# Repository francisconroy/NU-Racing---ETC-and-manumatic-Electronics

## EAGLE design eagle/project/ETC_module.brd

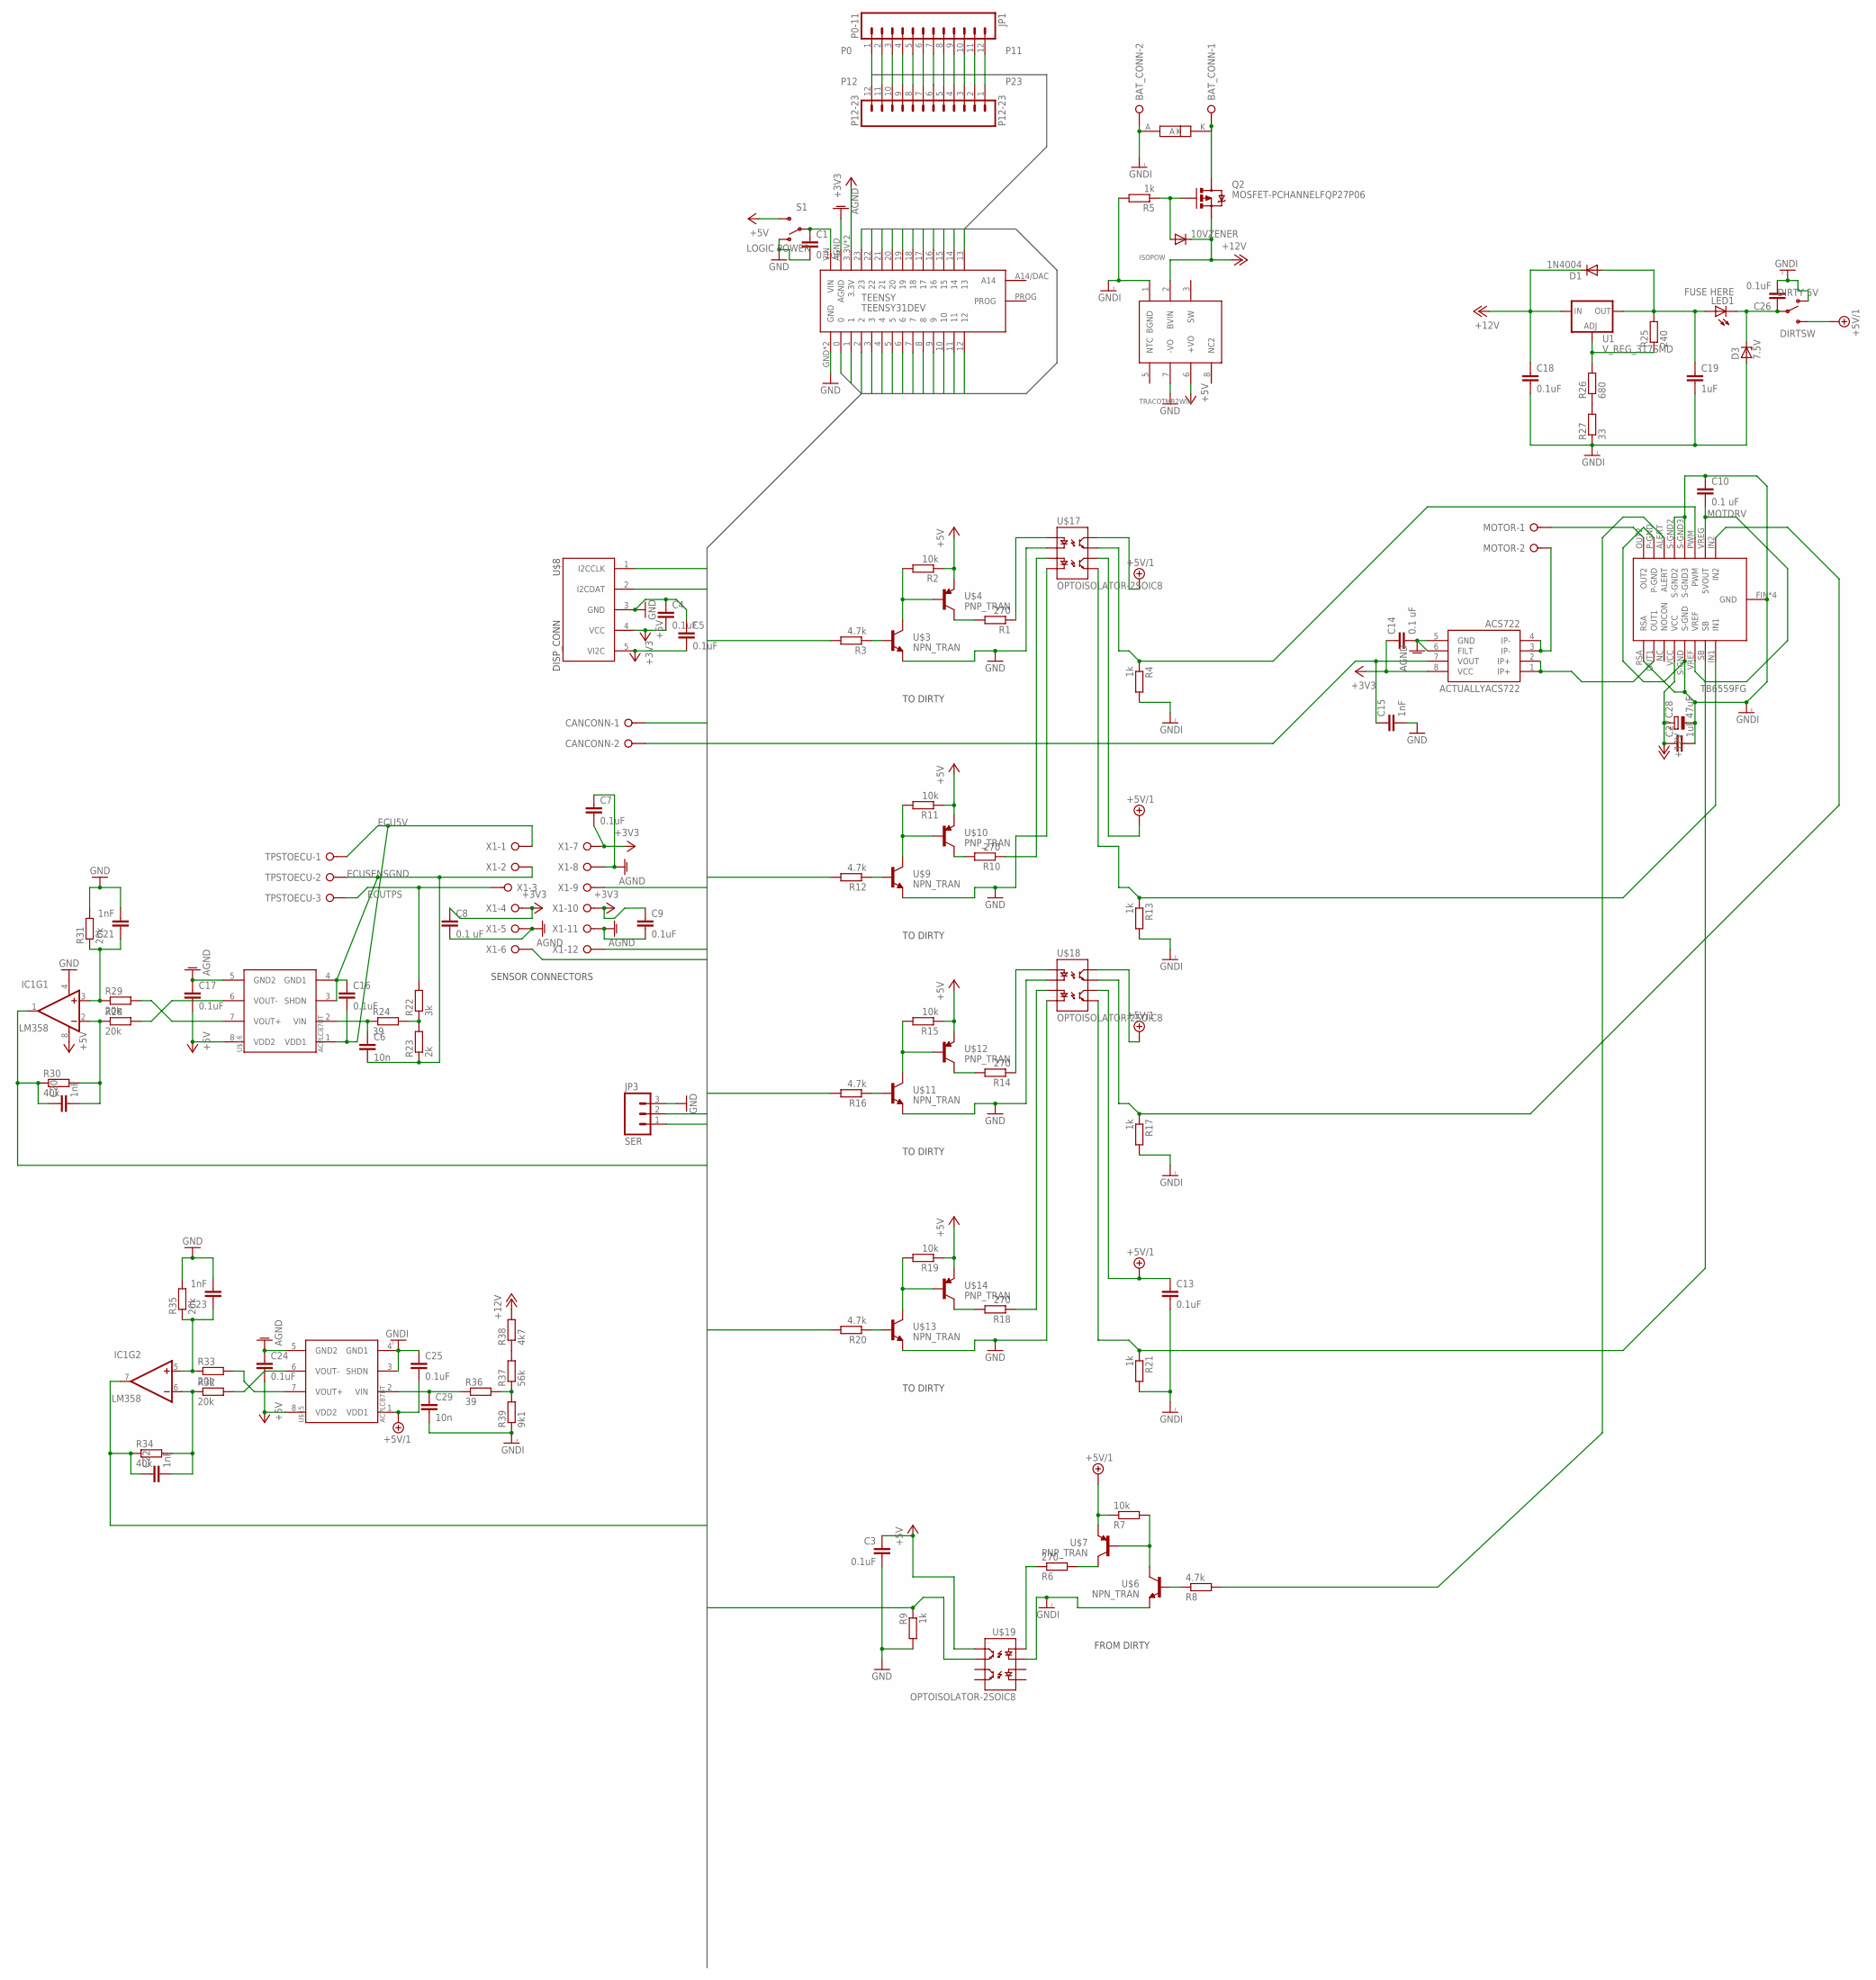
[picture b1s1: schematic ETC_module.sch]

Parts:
10VZENER: DIODE-DO214BA; DO214BA
ACTUALLYACS722: ACS722; SO08
BAT_CONN: W237-02P; W237-132
C1, C3, C4, C5, C7, C9, C13, C16, C17, C18, C24, C25, C26: 0.1uF; C1206
C6, C29: 10n; C1206
C8, C10, C14: 0.1 uF; C1206
C15, C20, C21, C22, C23: 1nF; C1206
C19, C27: 1uF; C1206
C28: 47uF; E5-8,5
CANCONN: W237-02P; W237-132
D1: 1N4004; DO41-10
D3: 7.5V; ZDIO-7.5
DIRTSW: DIRTY 5V; SWITCH-SPDT_KIT
IC1: LM358; DIP08
ISOPOW: TRACOTMR2WIN; TRACOPOWERDC-DCTRM2WIN
JP1: P0-11; 1X12_LOCK
JP3: SER; MOLEX-1X3_LOCK
LED1: FUSE HERE; LED-1206
MOTDRV: TB6559FG; HSOP16-P-300-1.00
MOTOR: W237-02P; W237-132
P12-23: P12-23; 1X12_LOCK
Q2: MOSFET-PCHANNELFQP27P06; TO220V
R1, R6, R10, R14, R18: 270; R1206
R2, R7, R11, R15, R19: 10k; R1206
R3, R8, R12, R16, R20: 4.7k; R1206
R4, R5, R9, R13, R17, R21: 1k; R1206
R22: 3k; M1206
R23: 2k; M1206
R24, R36: 39; R1206
R25: 240; R1206
R26: 680; R1206
R27: 33; R1206
R28, R29, R31, R32, R33, R35: 20k; R1206
R30, R34: 40k; R1206
R37: 56k; R1206
R38: 4k7; R1206
R39: 9k1; R1206
S1: LOGIC POWER; SWITCH-SPDT_KIT
TEENSY: TEENSY31DEV; TEENSY31PAC
TPSTOECU: W237-03P; W237-133
U1: V_REG_317SMD; SOT223
U$1: LNBTVS; JEDECDO-214AB
U$3, U$6, U$9, U$11, U$13: NPN_TRAN; SOT23-3
U$4, U$7, U$10, U$12, U$14: PNP_TRAN; SOT23-3
U$8: DISP_CONN
U$15, U$16: ACPLC87BT; SO8STRETCH
U$17, U$18, U$19: OPTOISOLATOR-2SOIC8; SO08-2
X1: W237-12P

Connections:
5VOUT: C10.2, MOTDRV.VREF, MOTDRV.VREG (5VOUT)
+3V3: ACTUALLYACS722.8 (VCC), C5.2, C7.2, C8.1, C9.1, C14.1, TEENSY.3.3V, TEENSY.3.3VV (3.3V), U$8.5 (VI2C), X1.4, X1.7, X1.10
+5V/1: C13.1, C25.2, DIRTSW.3 (S), R7.1, U$7.2 (E), U$15.1 (VDD1), U$17.6 (CL2), U$17.8 (CL1), U$18.6 (CL2), U$18.8 (CL1)
+5VCLEAN: C3.1, C4.2, C17.2, C24.2, IC1.8 (V+), ISOPOW.6 (+VO), R2.1, R11.1, R15.1, R19.1, S1.3 (S), U$4.2 (E), U$8.4 (VCC), U$10.2 (E), U$12.2 (E), U$14.2 (E), U$15.8 (VDD2), U$16.8 (VDD2), U$19.8 (CL1)
AGND: ACTUALLYACS722.5 (GND), ACTUALLYACS722.6 (FILT), C7.1, C8.2, C9.2, C14.2, C17.1, C24.1, TEENSY.AGND, U$15.5 (GND2), U$16.5 (GND2), X1.5, X1.8, X1.11
ECU5V: C16.2, TPSTOECU.1, U$16.1 (VDD1), X1.1
ECUSENSGND: C6.2, C16.1, R23.1, TPSTOECU.2, U$16.3 (SHDN), U$16.4 (GND1), X1.2
ECUTPS: R22.2, TPSTOECU.3, X1.3
GND: C1.2, C3.2, C4.1, C5.1, C15.2, C21.2, C23.2, IC1.4 (V-), ISOPOW.7 (-VO), JP3.3, R9.2, R31.2, R35.2, S1.1 (O), TEENSY.GND, TEENSY.GND2 (GND), U$3.2 (E), U$8.3 (GND), U$9.2 (E), U$11.2 (E), U$13.2 (E), U$17.2 (C1), U$17.4 (C2), U$18.2 (C1), U$18.4 (C2)
GNDI: BAT_CONN.2, C10.1, C13.2, C18.2, C19.2, C25.1, C26.2, C27.2, C28.-, C29.2, D3.A, DIRTSW.1 (O), ISOPOW.1 (BGND), MOTDRV.FIN (GND), MOTDRV.FIN2 (GND), MOTDRV.P$4 (GND), MOTDRV.P$20 (GND), MOTDRV.P-GND, MOTDRV.RSA, MOTDRV.S-GND, MOTDRV.S-GND2, MOTDRV.S-GND3, R4.2, R5.2, R13.2, R17.2, R21.2, R27.1, R39.1, U$1.A, U$6.2 (E), U$15.3 (SHDN), U$15.4 (GND1), U$19.2 (C1)
unnamed: R2.2, U$3.3 (C), U$4.1 (B)
unnamed: C1.1, S1.2, TEENSY.VIN
unnamed: R1.1, U$17.1 (A1)
unnamed: R1.2, U$4.3 (C)
unnamed: R3.1, U$3.1 (B)
unnamed: R7.2, U$6.3 (C), U$7.1 (B)
unnamed: 10VZENER.A, Q2.1 (G), R5.1
unnamed: MOTDRV.PWM, R4.1, U$17.7 (EM1)
unnamed: R6.1, U$19.1 (A1)
unnamed: R6.2, U$7.3 (C)
unnamed: R8.1, U$6.1 (B)
unnamed: R19.2, U$13.3 (C), U$14.1 (B)
unnamed: R18.1, U$18.3 (A2)
unnamed: C26.1, D3.C, DIRTSW.2, LED1.C
unnamed: R37.2, R38.1
unnamed: C19.1, D1.A, LED1.A, R25.2, U1.2 (OUT)
unnamed: R11.2, U$9.3 (C), U$10.1 (B)
unnamed: MOTDRV.OUT2, MOTOR.1
unnamed: ACTUALLYACS722.1 (IP+), ACTUALLYACS722.2 (IP+), MOTDRV.OUT1
unnamed: R10.1, U$17.3 (A2)
unnamed: R10.2, U$10.3 (C)
unnamed: R12.1, U$9.1 (B)
unnamed: R15.2, U$11.3 (C), U$12.1 (B)
unnamed: R14.1, U$18.1 (A1)
unnamed: R14.2, U$12.3 (C)
unnamed: R16.1, U$11.1 (B)
unnamed: MOTDRV.IN2, R17.1, U$18.7 (EM1)
unnamed: R18.2, U$14.3 (C)
unnamed: R20.1, U$13.1 (B)
unnamed: MOTDRV.ALERT, R8.2
unnamed: MOTDRV.SB, R21.1, U$18.5 (EM2)
unnamed: ACTUALLYACS722.3 (IP-), ACTUALLYACS722.4 (IP-), MOTOR.2
unnamed: C6.1, R24.1, U$16.2 (VIN)
unnamed: R22.1, R23.2, R24.2
unnamed: R26.1, R27.2
unnamed: R25.1, R26.2, U1.1 (ADJ)
unnamed: R36.2, R37.1, R39.2
unnamed: C23.1, IC1.5 (+IN), R33.1, R35.1
unnamed: C22.2, IC1.6 (-IN), R32.1, R34.2
unnamed: R32.2, U$15.6 (VOUT-)
unnamed: MOTDRV.IN1, R13.1, U$17.5 (EM2)
unnamed: R29.2, U$16.7 (VOUT+)
unnamed: C21.1, IC1.3 (+IN), R29.1, R31.1
unnamed: C20.2, IC1.2 (-IN), R28.1, R30.2
unnamed: R28.2, U$16.6 (VOUT-)
unnamed: C29.1, R36.1, U$15.2 (VIN)
unnamed: R33.2, U$15.7 (VOUT+)
P0: JP1.1, JP3.1, TEENSY.0
P1: JP1.2, JP3.2, TEENSY.1
P2: JP1.3, TEENSY.2
P3: CANCONN.1, JP1.4, TEENSY.3
P4: CANCONN.2, JP1.5, TEENSY.4
P5: JP1.6, R9.1, TEENSY.5, U$19.7 (EM1)
P6: JP1.7, R3.2, TEENSY.6
P7: JP1.8, R12.2, TEENSY.7
P8: JP1.9, R16.2, TEENSY.8
P9: JP1.10, R20.2, TEENSY.9
P10: JP1.11, TEENSY.10
P11: JP1.12, TEENSY.11
P12: P12-23.12, TEENSY.12
P13: P12-23.11, TEENSY.13
P14: P12-23.10, TEENSY.14, X1.9
P15: P12-23.9, TEENSY.15, X1.12
P16: C20.1, IC1.1 (OUT), P12-23.8, R30.1, TEENSY.16
P17: P12-23.7, TEENSY.17, X1.6
P18: P12-23.6, TEENSY.18, U$8.2 (I2CDAT)
P19: P12-23.5, TEENSY.19, U$8.1 (I2CCLK)
P20: P12-23.4, TEENSY.20
P21: C22.1, IC1.7 (OUT), P12-23.3, R34.1, TEENSY.21
P22: ACTUALLYACS722.7 (VOUT), C15.1, P12-23.2, TEENSY.22
P23: P12-23.1, TEENSY.23

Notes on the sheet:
TO DIRTY
FROM DIRTY
SENSOR CONNECTORS

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
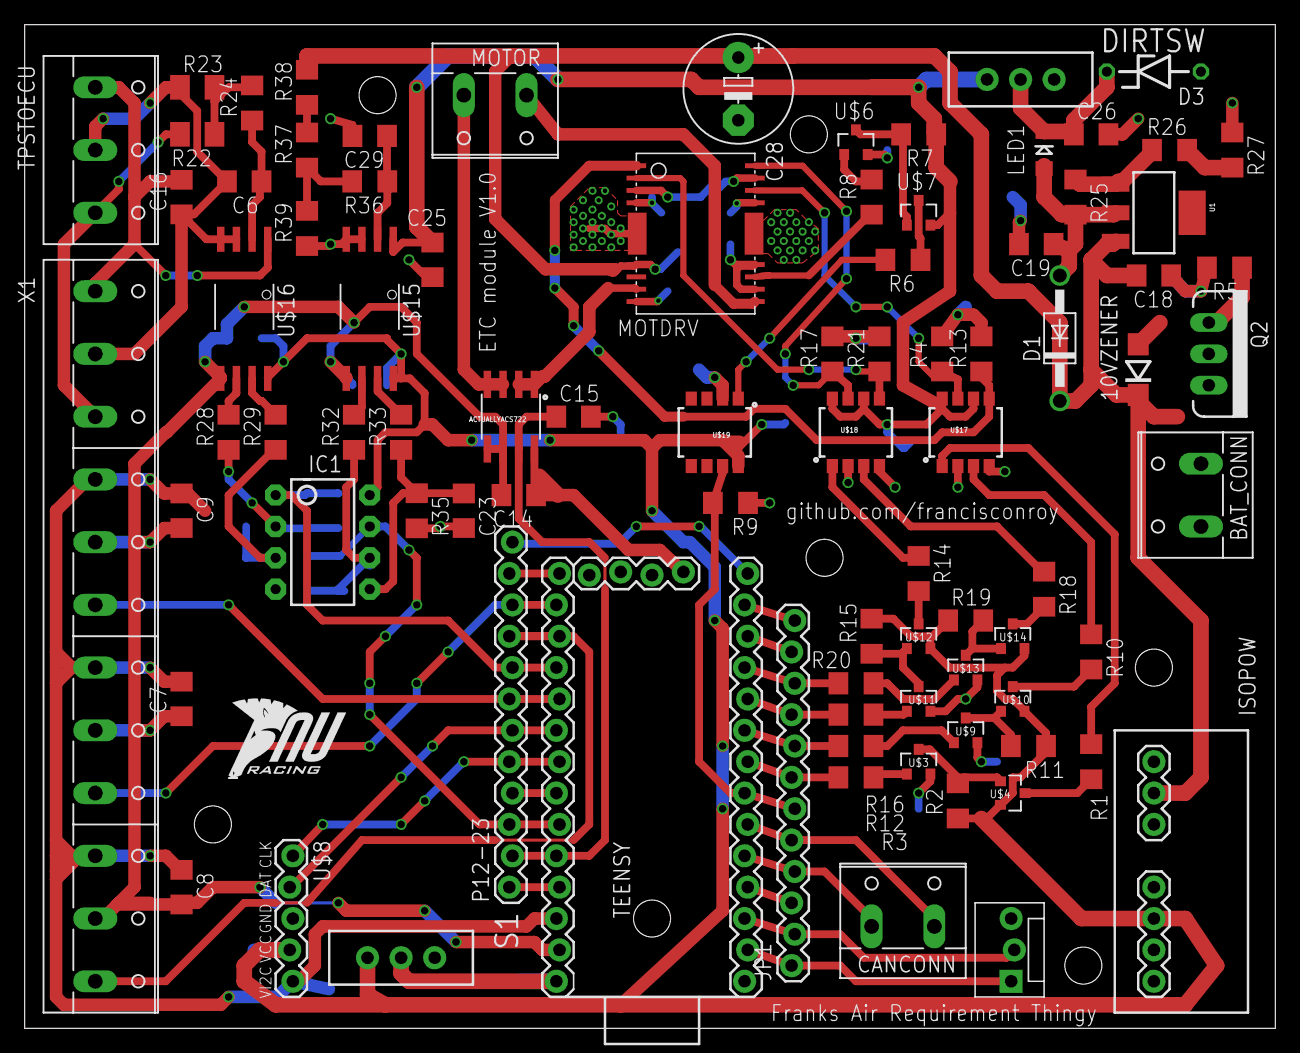
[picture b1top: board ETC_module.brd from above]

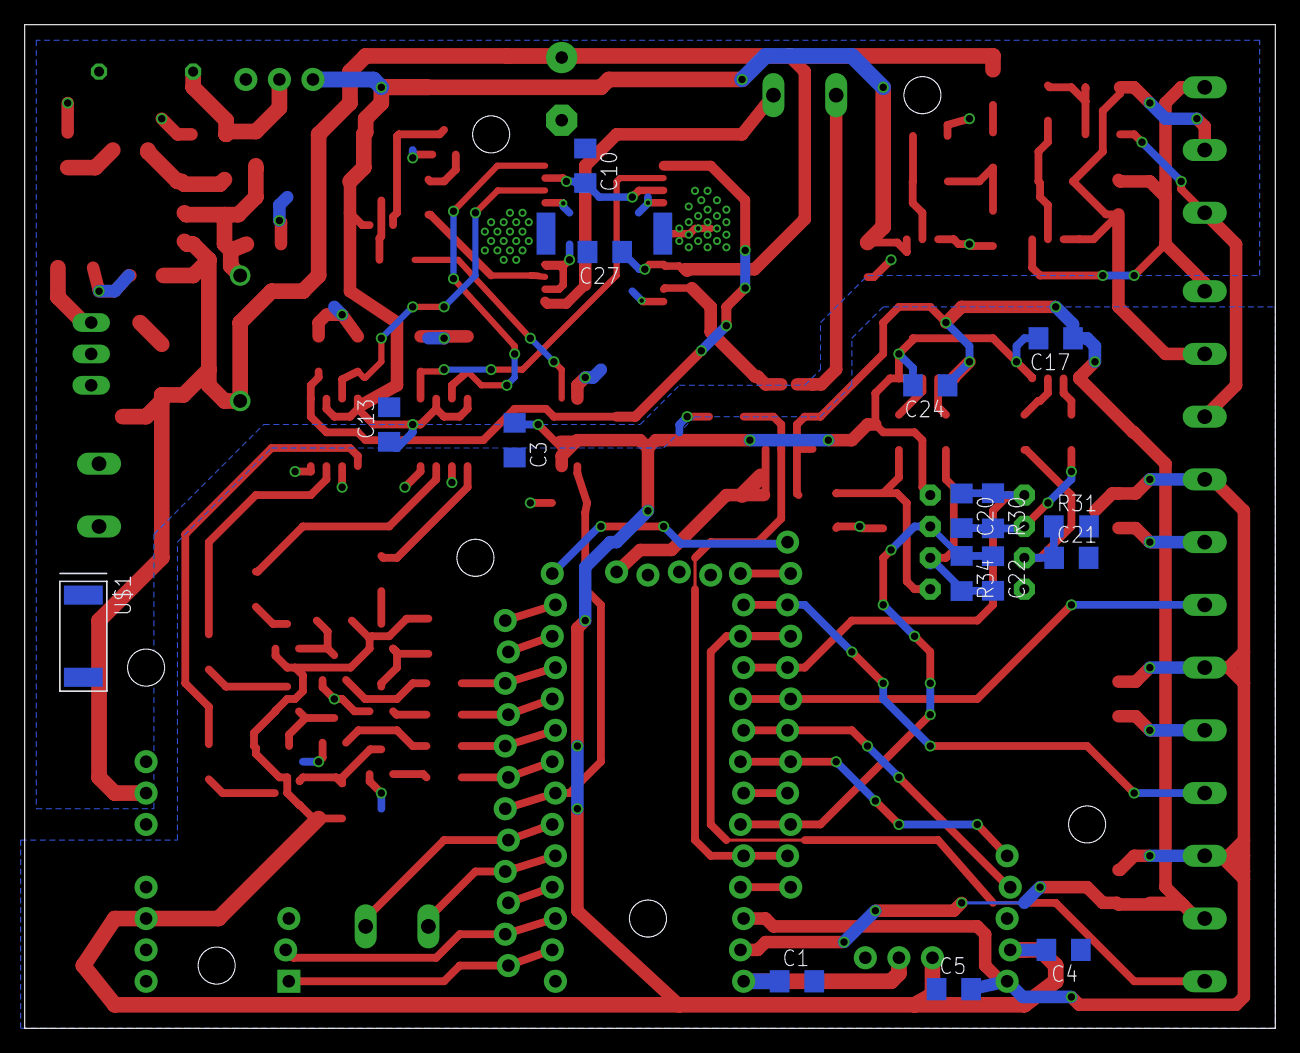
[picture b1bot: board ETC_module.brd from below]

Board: 2 copper layers, 101.3 x 81.3 mm, 104 parts (16 on the bottom side), 83 nets.

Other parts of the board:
U$20: NURLOGO

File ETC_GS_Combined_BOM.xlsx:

Sum of qty
pkg | value | Total | TOTAL_REQ | ON_HAND | SUPPLIER# | PRICE PER UNIT | NOTE | SUPPLIER
1X10_LOCK | (blank) | 2 | 2 | 0 | 588544 | 0.91500000000000004 | MTA-100 conn | E14
1X12_LOCK | P0-11 | 2 | 0
 | P12-23 | 2 | 0
C1206 | 0.1uF | 17 | 10 | 18 | 1867950 | 3.5999999999999997E-2 |  | E14
 | 10n | 2 | 4 |  | 4801880 | 2.8000000000000001E-2 |  | E14
 | 1nF | 5 | 10 |  | 1759337 | 7.3999999999999996E-2 |  | E14
 | 1uF | 2 | 4 |  | 1759438 | 1.7999999999999999E-2 |  | E14
DIP08 | LM358 | 1 | 2 |  | SF-COM-09456 | 1.46 | Through little bird elec | LittleBird
DISP_CONN | DISP_CONN | 1 | 1 |  | 588600 | 0.42799999999999999 | display header | E14
DO214BA | 0 | 1 | 4 |  | 1687497 | 0.56000000000000005 | 10V ZENER | E14
 | (blank) | 1
DO41-10 | 1N4004 | 1 | 2 |  | 1383892 | 6.7000000000000004E-2 |  | E14
E5-8,5 | 47uF | 1 | 2 |  | 2346630 | 0.98899999999999999 |  | E14
HSOP16-P-300-1.00 | TB6559FG | 1 | 0
JEDECDO-214AB | LNBTVS | 2 | 4 |  | 1749287 | 1.88 |  | E14
LED-1206 | FUSE HERE | 1 | 10 |  | 2414111 | 0.26200000000000001 | FUSE 500mA for LM7805 | E14
M1206 | 2k | 1 | 2 |  | 2333590 | 0.1 |  | E14
 | 3k | 1 | 2 |  | 1646697 | 3.3999999999999998E-3 |  | E14
MOLEX-1X3_LOCK | SER | 2 | 4 |  | 588581 | 0.33100000000000002 | MTA-100 serial | E14
R1206 | 15 | 2 | 4 |  | 2332114 | 7.0000000000000007E-2 |  | E14
 | 27 | 2 | 4 |  | 2332118 | 7.0000000000000007E-2 |  | E14
 | 33 | 1 | 2 |  | 1692544 | 0.04 |  | E14
 | 39 | 2 | 4 |  | 2332120 | 7.0000000000000007E-2 |  | E14
 | 240 | 1 | 2 |  | 1630578 | 8.9999999999999993E-3 |  | E14
 | 270 | 6 | 12 |  | 1470003 | 0.04 |  | E14
 | 680 | 1 | 2 |  | 1632597 | 1.7999999999999999E-2 |  | E14
 | 10k | 15 | 30 |  | 1632523 | 8.0000000000000002E-3 |  | E14
 | 1k | 8 | 16 |  | 1811972 | 2.1000000000000001E-2 |  | E14
 | 20k | 6 | 12 |  | 1632543 | 8.9999999999999993E-3 |  | E14
 | 4.7k | 7 | 14 |  | 1632579 | 2.1999999999999999E-2 |  | E14
 | 40k | 2 | 4 |  | 2142268 | 0.02 |  | E14
 | 56k | 1 | 2 |  | 1158086 | 0.05 |  | E14
 | 9k1 | 1 | 2 |  | 1153324 | 0.23 |  | E14
SO08 | ACS722 | 1 | 2 |  |  |  | PURCHASE THROUGH DIGIKEY - ALLEGRO ACS722LLCTR-05AB-T
SO08-2 | OPTOISOLATOR-2SOIC8 | 4 | 8 |  | 1045451 | 2.96 |  | E14
SO8STRETCH | ACPLC87BT | 2 | 4 |  | 2313197 | 22.63 |  | E14
SOT223 | V_REG_317SMD | 1 | 2 |  | 1652366 | 0.95299999999999996 | FAN1117 SOT223 or sparkfun#COM-00595 | E14
SOT23-3 | NPN_TRAN | 6 | 12 |  | 1459098 | 0.16500000000000001 |  | E14
 | PNP_TRAN | 6 | 12 |  | 1459099 | 0.16500000000000001 |  | E14
SWITCH-SPDT_KIT | DIRTY 5V | 1 | 2 |  | 1524325 | 2.21 |  | E14
 | LOGIC POWER | 2 | 4 |  | 1524325 | 2.21 |  | E14
TEENSY31PAC | TEENSY31DEV | 2 | 0
TO220V | MOSFET-PCHANNELFQP27P06 | 2 | 4 |  | 9846530 | 2.67 |  | E14
TRACOPOWERDC-DCTRM2WIN | TRACOTMR2WIN | 2 | 3 |  | 1205065 | 25.3 | Alternate TMR 1211 | E14
W237-12P | 0 | 1 | 2 |  | 2315261 | 6.51 |  | E14
W237-132 | 0 | 5 | 12 |  | 2493625 | 0.66 |  | E14
W237-133 | 0 | 5 | 12 |  | 2493626 | 0.98 |  | E14
W237-5P | 0 | 1 | 0
ZDIO-7.5 | 7.5V | 1 | 1 |  | 4534633 | 0.188 |  | E14
(blank) | (blank)
Grand Total |  | 143 | 253
 |  |  | EXTRA
 |  |  | 4 |  | 1296705 | 1.58 | MTA-100 plug 26AWG | E14
 |  |  | 1 |  | AF-878 | 15.09 | Adafruit 0.56 4-Digit 7-Segment Display w/I2C Backpack - Red | LittleBird
 |  |  | 2 |  | 1098711 | 0.52600000000000002 | MTA-100 plug 26AWG | E14
 |  |  | 2 |  | 1773007 | 0.81699999999999995 | MTA-100 plug 22AWG | E14
 |  |  | 3 |  | 1387715 | 5.05 | 5 core display cable 22 AWG | E14
 |  |  | 2 |  | 1301033 | 4.3600000000000003 | 10 ribbon cable | E14

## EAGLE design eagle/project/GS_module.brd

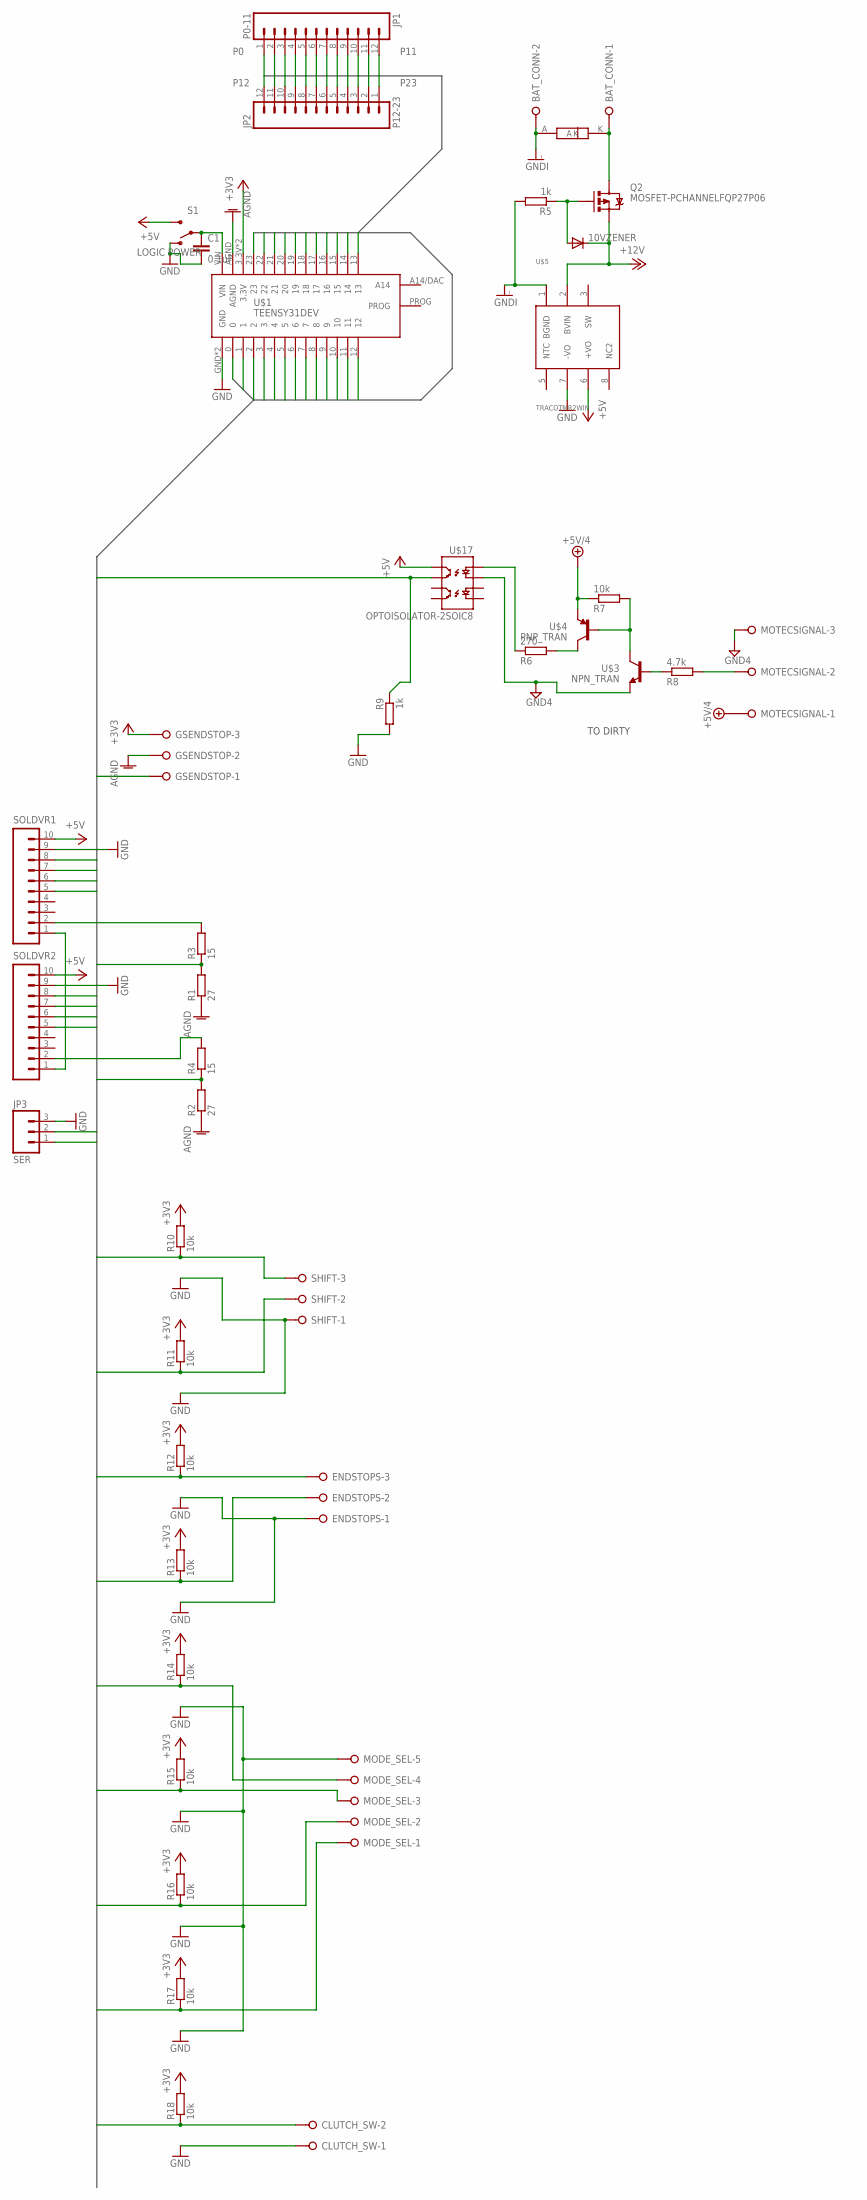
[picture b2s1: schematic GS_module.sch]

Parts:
10VZENER: DIODE-DO214BA; DO214BA
BAT_CONN: W237-02P; W237-132
C1: 0.1uF; C1206
CLUTCH_SW: W237-02P; W237-132
ENDSTOPS: W237-03P; W237-133
GSENDSTOP: W237-03P; W237-133
JP1: P0-11; 1X12_LOCK
JP2: P12-23; 1X12_LOCK
JP3: SER; MOLEX-1X3_LOCK
MODE_SEL: W237-05P; W237-5P
MOTECSIGNAL: W237-03P; W237-133
Q2: MOSFET-PCHANNELFQP27P06; TO220V
R1, R2: 27; R1206
R3, R4: 15; R1206
R5, R9: 1k; R1206
R6: 270; R1206
R7, R10, R11, R12, R13, R14, R15, R16, R17, R18: 10k; R1206
R8: 4.7k; R1206
S1: LOGIC POWER; SWITCH-SPDT_KIT
SHIFT: W237-03P; W237-133
SOLDVR1, SOLDVR2: M10LOCK; 1X10_LOCK
U$1: TEENSY31DEV; TEENSY31PAC
U$3: NPN_TRAN; SOT23-3
U$4: PNP_TRAN; SOT23-3
U$5: TRACOTMR2WIN; TRACOPOWERDC-DCTRM2WIN
U$6: LNBTVS; JEDECDO-214AB
U$17: OPTOISOLATOR-2SOIC8; SO08-2

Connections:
+3V3: GSENDSTOP.3, R10.2, R11.2, R12.2, R13.2, R14.2, R15.2, R16.2, R17.2, R18.2, U$1.3.3V, U$1.3.3VV (3.3V)
+5V: S1.3 (S), SOLDVR1.10, SOLDVR2.10, U$5.6 (+VO), U$17.8 (CL1)
+5V/4: MOTECSIGNAL.1, R7.1, U$4.2 (E)
+12V: 10VZENER.C, Q2.3 (S), U$5.2 (BVIN)
AGND: GSENDSTOP.2, R1.1, R2.1, U$1.AGND
GND: C1.2, CLUTCH_SW.1, ENDSTOPS.1, JP3.3, MODE_SEL.5, R9.2, S1.1 (O), SHIFT.1, SOLDVR1.9, SOLDVR2.9, U$1.GND, U$1.GND2 (GND), U$5.7 (-VO)
GND4: MOTECSIGNAL.3, U$3.2 (E), U$17.2 (C1)
GNDI: BAT_CONN.2, R5.2, U$5.1 (BGND), U$6.A
unnamed: R7.2, U$3.3 (C), U$4.1 (B)
unnamed: C1.1, S1.2, U$1.VIN
unnamed: R3.2, SOLDVR1.2
unnamed: R6.1, U$17.1 (A1)
unnamed: R4.2, SOLDVR2.2
unnamed: R6.2, U$4.3 (C)
unnamed: 10VZENER.A, Q2.1 (G), R5.1
unnamed: R8.1, U$3.1 (B)
unnamed: MOTECSIGNAL.2, R8.2
unnamed: SOLDVR1.1, SOLDVR2.1
unnamed: BAT_CONN.1, Q2.2 (D), U$6.K
P0: JP1.1, JP3.1, U$1.0
P1: JP1.2, JP3.2, U$1.1
P2: JP1.3, SOLDVR1.5, U$1.2
P3: JP1.4, SOLDVR1.8, U$1.3
P4: JP1.5, SOLDVR1.7, U$1.4
P5: JP1.6, SOLDVR1.6, U$1.5
P6: CLUTCH_SW.2, JP1.7, R18.1, U$1.6
P7: JP1.8, SOLDVR2.5, U$1.7
P8: JP1.9, SOLDVR2.8, U$1.8
P9: JP1.10, SOLDVR2.7, U$1.9
P10: JP1.11, SOLDVR2.6, U$1.10
P11: JP1.12, R10.1, SHIFT.3, U$1.11
P12: JP2.12, R11.1, SHIFT.2, U$1.12
P13: JP2.11, R9.1, U$1.13, U$17.7 (EM1)
P14: GSENDSTOP.1, JP2.10, U$1.14
P15: JP2.9, U$1.15
P16: JP2.8, R1.2, R3.1, U$1.16
P17: ENDSTOPS.3, JP2.7, R12.1, U$1.17
P18: ENDSTOPS.2, JP2.6, R13.1, U$1.18
P19: JP2.5, R2.2, R4.1, U$1.19
P20: JP2.4, MODE_SEL.4, R14.1, U$1.20
P21: JP2.3, MODE_SEL.3, R15.1, U$1.21
P22: JP2.2, MODE_SEL.2, R16.1, U$1.22
P23: JP2.1, MODE_SEL.1, R17.1, U$1.23

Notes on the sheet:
TO DIRTY

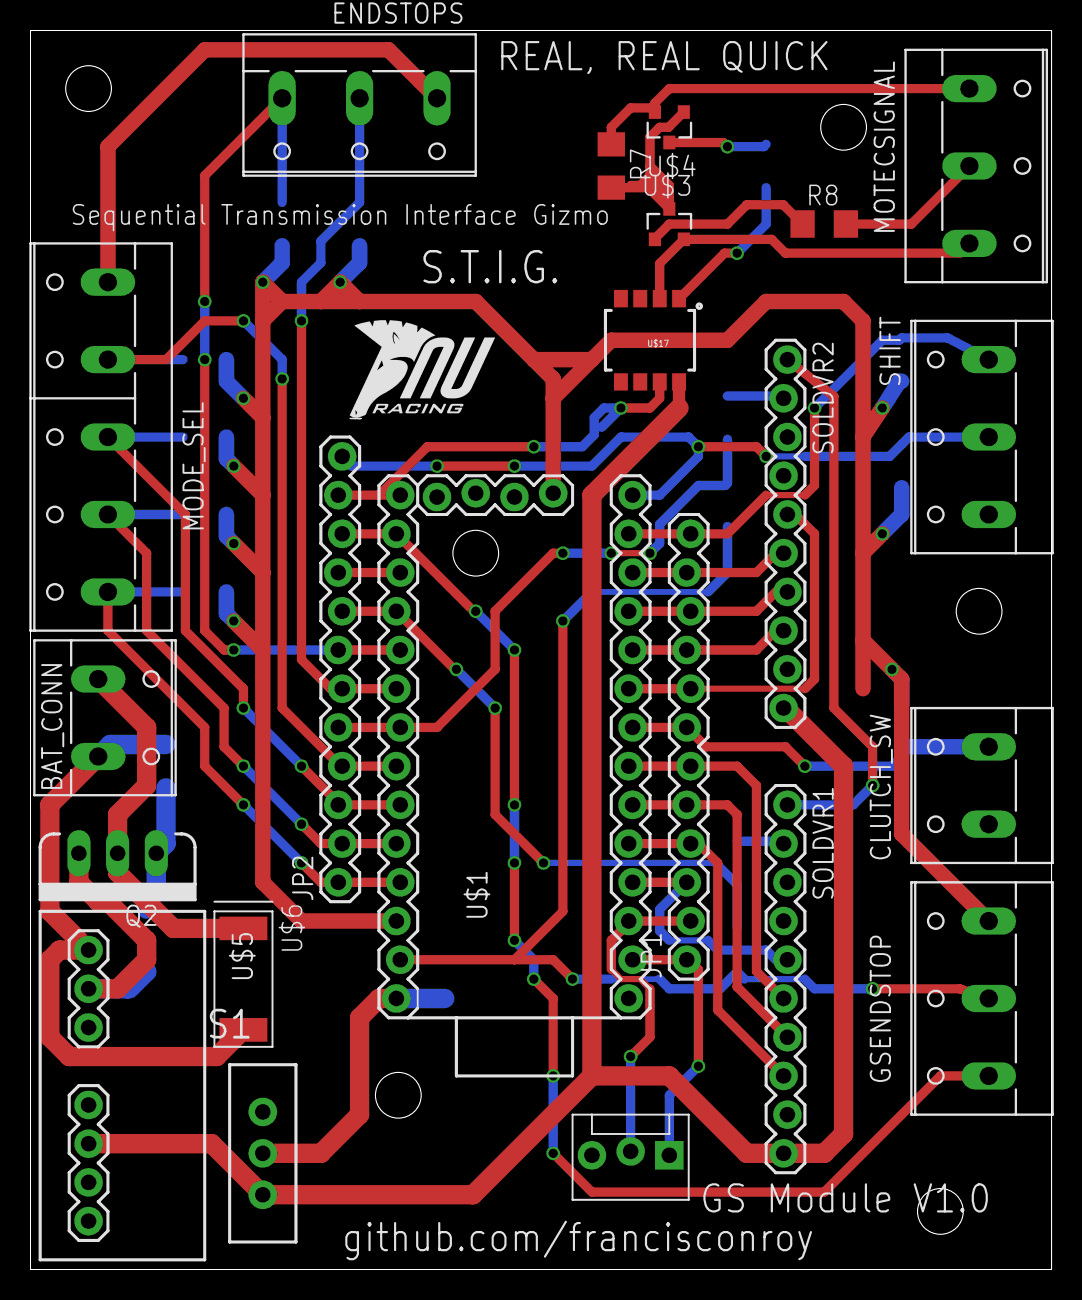
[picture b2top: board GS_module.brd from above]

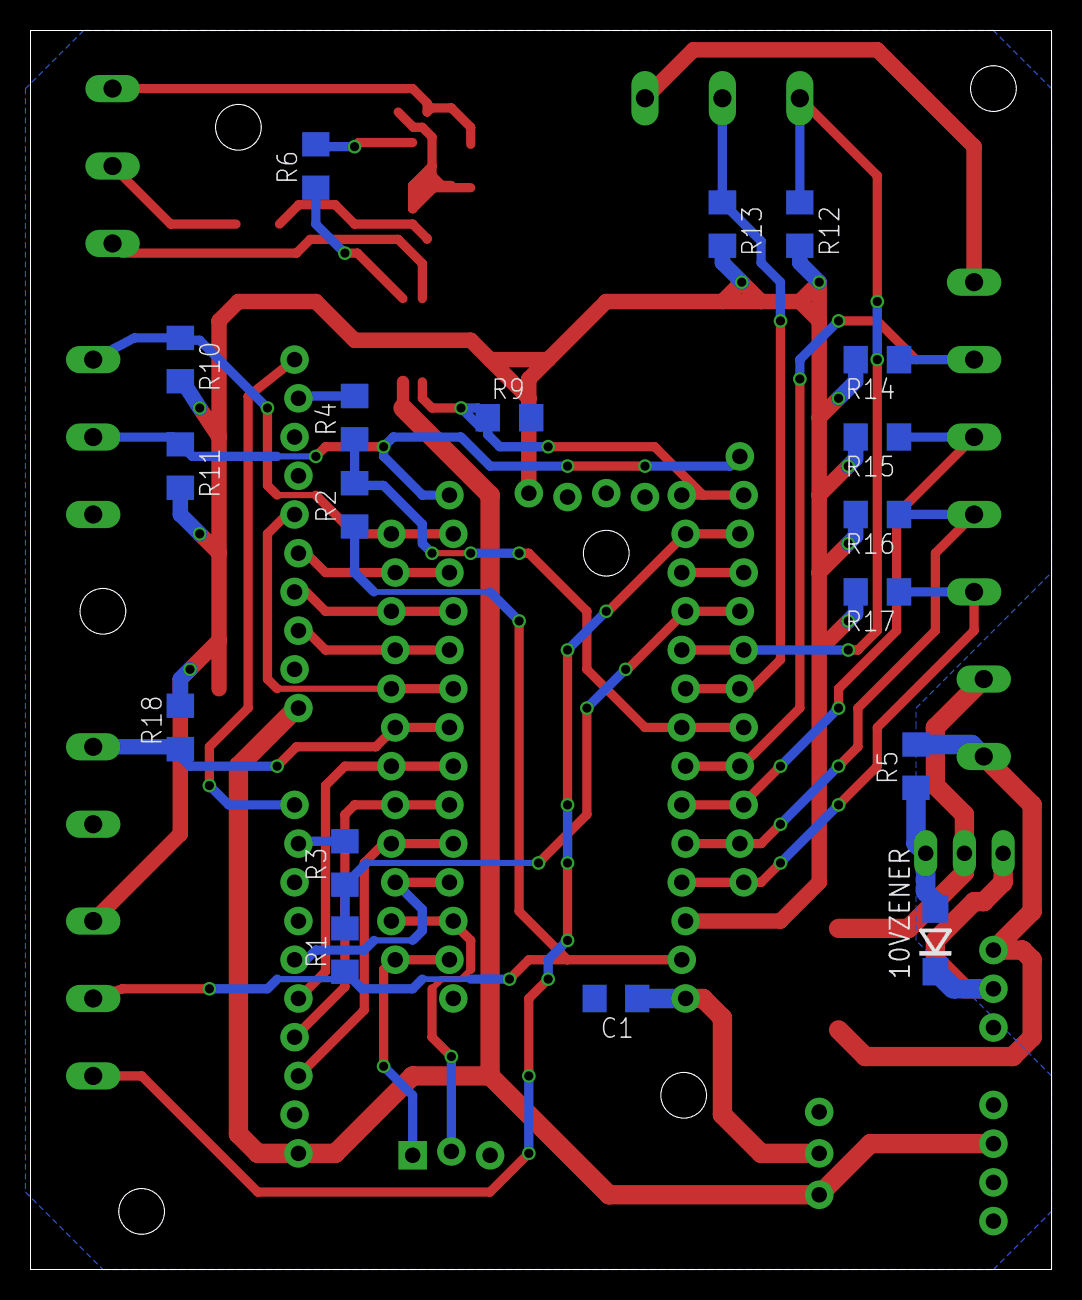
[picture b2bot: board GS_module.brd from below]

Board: 2 copper layers, 67.0 x 81.3 mm, 41 parts (18 on the bottom side), 43 nets.

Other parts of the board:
U$2: NURLOGO

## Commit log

2015-08-13 Initial commit to repo
    Commit ETC PCB layout as version 1.0
2015-08-16 v1.0 of ETC board complete
    initial work on GS board underway too
2015-08-19 finish version 1.0 of GS board
    yay!
2015-09-01 Versions of the board which went to the fab house
    Updating BOMS for component ordering
2015-09-01 more BOM work
    working on the BOMs
2015-09-22 update
    make pdf
2015-09-28 update for hardware construction
2015-10-09 update for connectors
    upd
2015-10-15 update connectors
2015-11-01 update at harness master
    update at harness master
2015-11-08 Update PINouts for testing
    update pinouts for new software developments
2015-11-25 update to fix reverse polarity protection
    FLIP DS on FET, only done on ETC schematic
2015-12-01 Updates with wiring updates
    Woop
2015-12-18 update before comp
    Updates

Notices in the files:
parts and their libraries:
SparkFun-AnalogIC: Licensing:Creative Commons ShareAlike 4.0 International - https://creativecommons.org/licenses/by-sa/4.0
